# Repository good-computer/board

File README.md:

Schematic and board layout for GOOD COMPUTER (r3).

These have been used to make real boards, so its not wrong, but I don't claim its right either.

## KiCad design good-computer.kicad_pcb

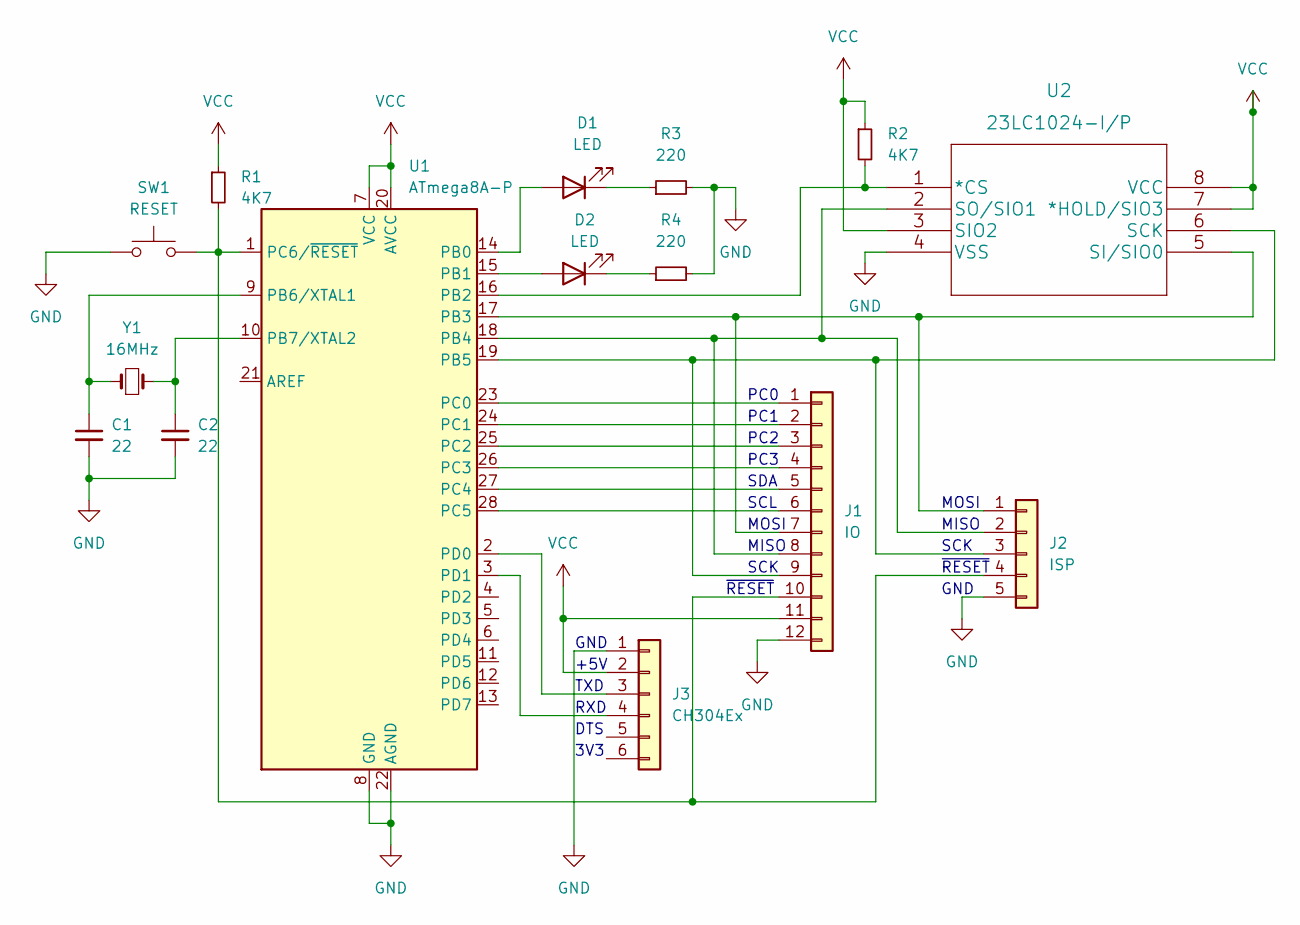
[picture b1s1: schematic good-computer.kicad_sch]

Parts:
C1, C2: 22; C_Disc_D3.0mm_W1.6mm_P2.50mm
D1, D2: LED; LED_D5.0mm
J1: IO; PinHeader_1x12_P2.54mm_Vertical
J2: ISP; PinHeader_1x05_P2.54mm_Vertical
J3: CH304Ex; PinHeader_1x06_P2.54mm_Vertical
R1, R2: 4K7; R_Axial_DIN0207_L6.3mm_D2.5mm_P7.62mm_Horizontal
R3, R4: 220; R_Axial_DIN0207_L6.3mm_D2.5mm_P7.62mm_Horizontal
SW1: RESET; SW_PUSH_6mm
U1: ATmega8A-P; DIP-28_W7.62mm
U2: 23LC1024-I/P; DIP-8_W7.62mm
Y1: 16MHz; Crystal_HC49-U_Vertical

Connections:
GND: C1.2, C2.2, J1.12, J2.5, J3.1, R3.2, R4.2, SW1.1, U1.8 (GND), U1.22 (AGND), U2.4 (VSS)
unnamed: C1.1, U1.9 (PB6/XTAL1), Y1.1
unnamed: C2.1, U1.10 (PB7/XTAL2), Y1.2
unnamed: D1.1 (K), R3.1
unnamed: D1.2 (A), U1.14 (PB0)
unnamed: D2.1 (K), R4.1
unnamed: D2.2 (A), U1.15 (PB1)
unnamed: J1.7, J2.1, U1.17 (PB3), U2.5 (SI/SIO0)
unnamed: J1.8, J2.2, U1.18 (PB4), U2.2 (SO/SIO1)
unnamed: J1.9, J2.3, U1.19 (PB5), U2.6 (SCK)
unnamed: J1.10, J2.4, R1.2, SW1.2, U1.1 (PC6/~RESET)
unnamed: J3.3, U1.2 (PD0)
unnamed: J3.4, U1.3 (PD1)
unnamed: R2.2, U1.16 (PB2), U2.1 (*CS)
unnamed: J1.1, U1.23 (PC0)
unnamed: J1.2, U1.24 (PC1)
unnamed: J1.3, U1.25 (PC2)
unnamed: J1.4, U1.26 (PC3)
unnamed: J1.5, U1.27 (PC4)
unnamed: J1.6, U1.28 (PC5)
VCC: J1.11, J3.2, R1.1, R2.1, U1.7 (VCC), U1.20 (AVCC), U2.3 (SIO2), U2.7 (*HOLD/SIO3), U2.8 (VCC)

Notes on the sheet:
DTS
3V3
PC3
PC2
GND
MOSI
RXD
SCK
MISO
TXD
+5V
~{RESET}
PC1
PC0
SDA
SCL

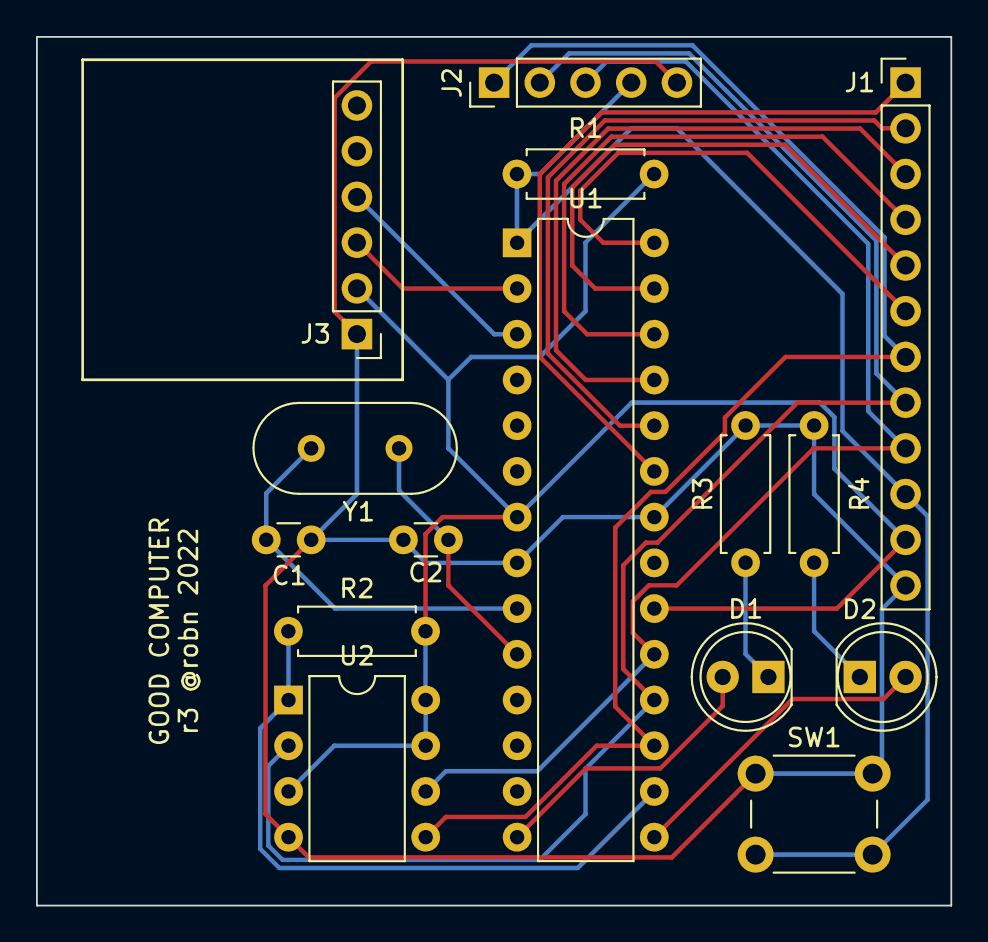
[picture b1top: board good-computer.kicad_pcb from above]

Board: 2 copper layers, 50.8 x 48.3 mm, 15 parts (0 on the bottom side), 21 nets.
